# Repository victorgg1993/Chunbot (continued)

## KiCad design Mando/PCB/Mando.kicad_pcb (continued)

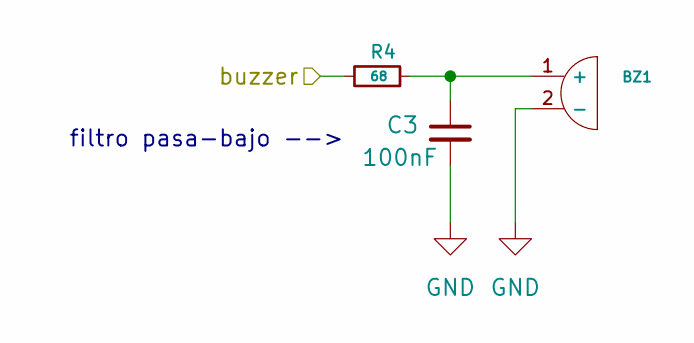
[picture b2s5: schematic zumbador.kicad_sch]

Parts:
BZ1: Buzzer_12x9.5RM7.6
C3: 100nF; C_0805_2012Metric_Pad1.18x1.45mm_HandSolder
R4: 68; R_0805_2012Metric

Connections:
GND: BZ1.2 (-), C3.2; also elsewhere on the board
unnamed: BZ1.1 (+), C3.1, R4.1
buzzer: R4.2; also elsewhere on the board

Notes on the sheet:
filtro pasa-bajo -->

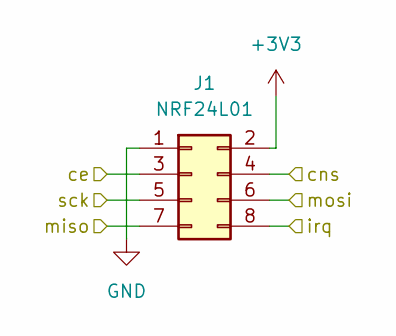
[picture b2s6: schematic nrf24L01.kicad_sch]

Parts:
J1: NRF24L01; PinHeader_2x04_P2.54mm_Vertical

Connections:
+3V3: J1.2; also elsewhere on the board
/NRF24L01/irq: J1.8
GND: J1.1; also elsewhere on the board
nrf_ce: J1.3; also elsewhere on the board
nrf_cns: J1.4; also elsewhere on the board
nrf_miso: J1.7; also elsewhere on the board
nrf_mosi: J1.6; also elsewhere on the board
nrf_sck: J1.5; also elsewhere on the board

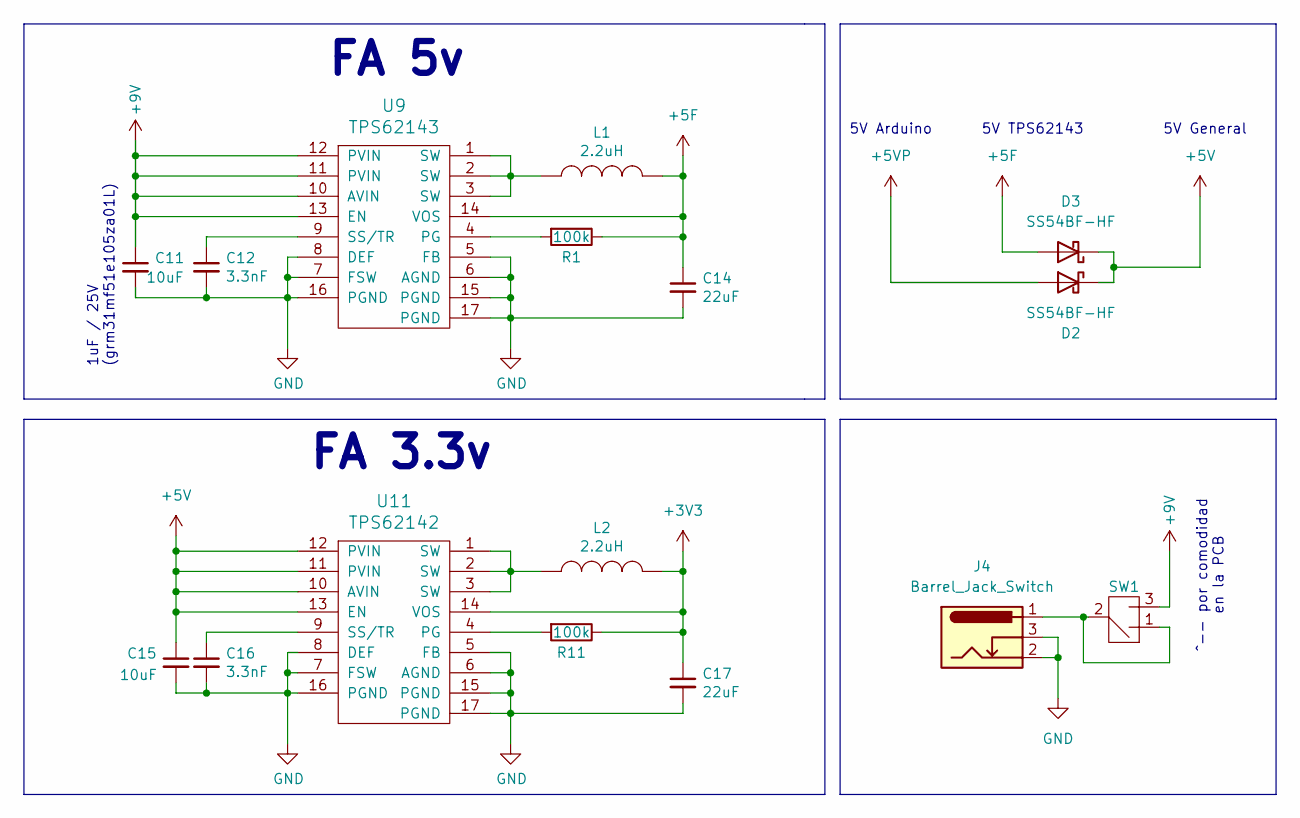
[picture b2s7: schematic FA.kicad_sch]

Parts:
C11: 10uF; C_1206_3216Metric_Pad1.33x1.80mm_HandSolder
C12, C16: 3.3nF; C_0805_2012Metric_Pad1.18x1.45mm_HandSolder
C14, C17: 22uF; C_0805_2012Metric_Pad1.18x1.45mm_HandSolder
C15: 10uF; C_0805_2012Metric_Pad1.18x1.45mm_HandSolder
D2, D3: SS54BF-HF; D_SMB_Handsoldering
J4: Barrel_Jack_Switch; POWER_JACK_SLOT
L1, L2: 2.2uH; L_Taiyo-Yuden_NR-50xx_HandSoldering
R1, R11: 100k; R_0805_2012Metric_Pad1.20x1.40mm_HandSolder
SW1: SS12D10
U9: TPS62143; QFN-16-1EP_3x3mm_P0.5mm_EP1.7x1.7mm
U11: TPS62142; QFN-16-1EP_3x3mm_P0.5mm_EP1.7x1.7mm

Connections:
+3V3: C17.1, L2.2, R11.1, U11.14 (VOS); also elsewhere on the board
+5F: C14.1, D3.2 (A), L1.2, R1.1, U9.14 (VOS)
+5V: C15.1, D2.1 (K), D3.1 (K), U11.10 (AVIN), U11.11 (PVIN), U11.12 (PVIN), U11.13 (EN); also elsewhere on the board
+5VP: D2.2 (A); also elsewhere on the board
+9V: C11.1, SW1.3, U9.10 (AVIN), U9.11 (PVIN), U9.12 (PVIN), U9.13 (EN)
GND: C11.2, C12.2, C14.2, C15.2, C16.2, C17.2, J4.2, J4.3, U9.5 (FB), U9.6 (AGND), U9.7 (FSW), U9.8 (DEF), U9.15 (PGND), U9.16 (PGND), U9.17 (PGND), U11.5 (FB), U11.6 (AGND), U11.7 (FSW), U11.8 (DEF), U11.15 (PGND), U11.16 (PGND), U11.17 (PGND); also elsewhere on the board
unnamed: J4.1, SW1.1, SW1.2
unnamed: L1.1, U9.1 (SW), U9.2 (SW), U9.3 (SW)
unnamed: L2.1, U11.1 (SW), U11.2 (SW), U11.3 (SW)
unnamed: R1.2, U9.4 (PG)
unnamed: C12.1, U9.9 (SS/TR)
unnamed: R11.2, U11.4 (PG)
unnamed: C16.1, U11.9 (SS/TR)

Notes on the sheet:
5V TPS62143
5V General
FA 5v
FA 3.3v
^-- por comodidad en la PCB
5V Arduino
1uF / 25V (grm31mf51e105za01L)

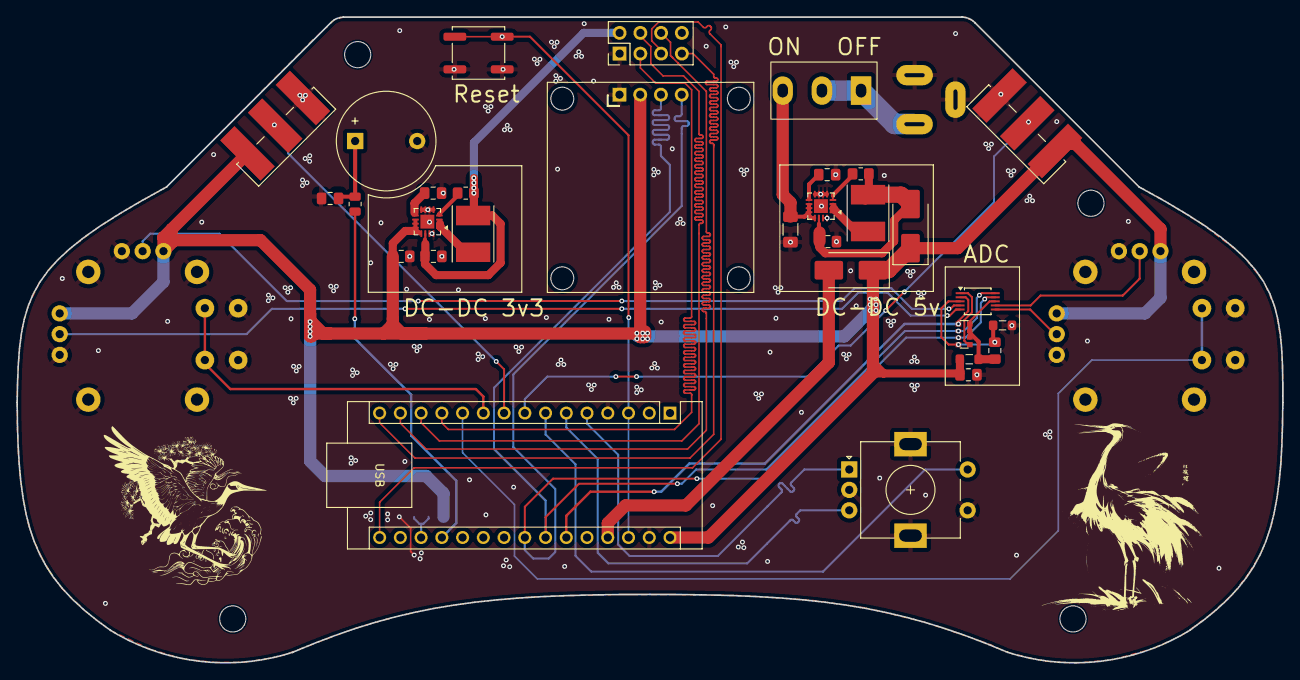
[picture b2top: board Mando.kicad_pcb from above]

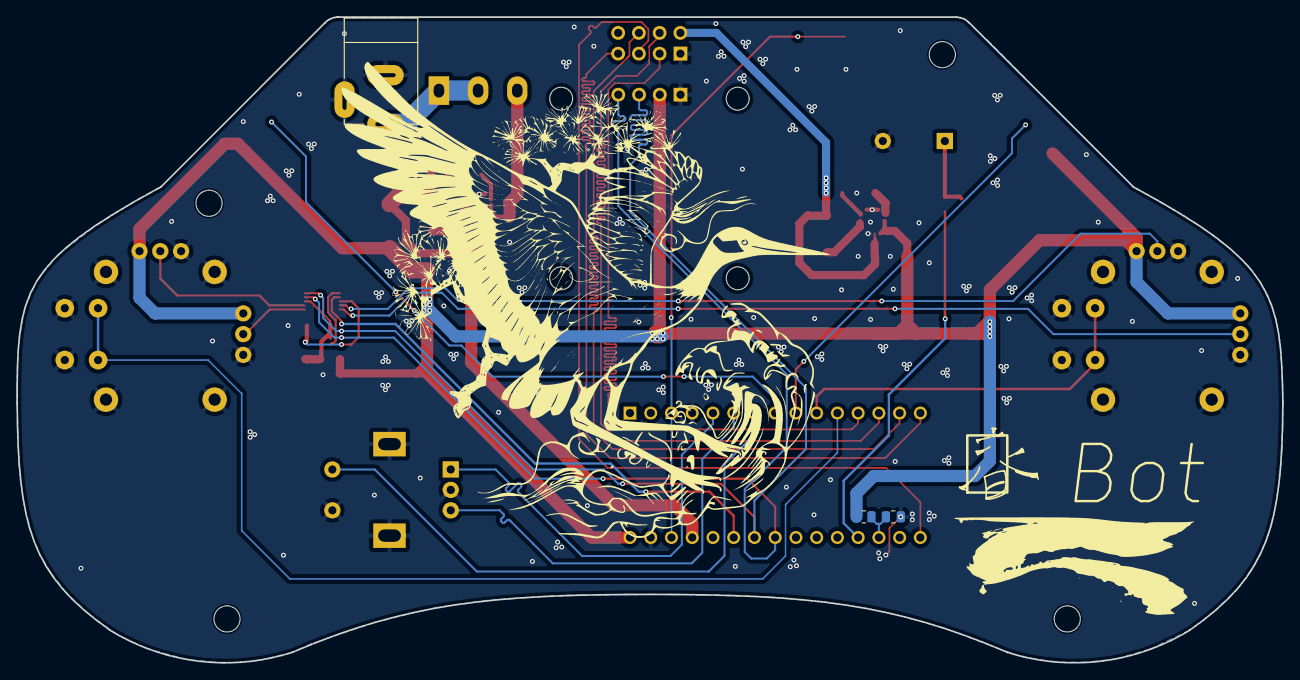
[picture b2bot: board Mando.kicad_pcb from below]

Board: 2 copper layers, 155.0 x 79.1 mm, 36 parts (3 on the bottom side), 39 nets.

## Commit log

2026-03-26 [Added] PCB del mando
2026-03-26 [Added] 3D del mando
2026-03-27 [Added] Ejemplos de codigo para el mando del robot
2026-03-27 [Added] 3D robot
2026-03-27 [Added] PCB robot
2026-03-27 [Added] Librerias necesarias
2026-03-27 [Modified] Cambio serigrafia para soporte de sensor de temperatura TMP36
2026-03-28 [Added] Ficheros readme con informacion del robot
2026-03-28 [Added] Tabla con los pines del mando
2026-03-28 [Added] Tutorial instalacion librerias. Tutorial instalacion elegir dispositivo.
2026-03-28 [Added] Explicacion instalacion dispositivos USB.
2026-03-28 [Added] Codigos de ejemplo del robot
2026-03-29 [Added] Imagenes + formateo markdown
2026-04-02 [Improved] Inicializacion serial para ver mensajes del modulo de radio
